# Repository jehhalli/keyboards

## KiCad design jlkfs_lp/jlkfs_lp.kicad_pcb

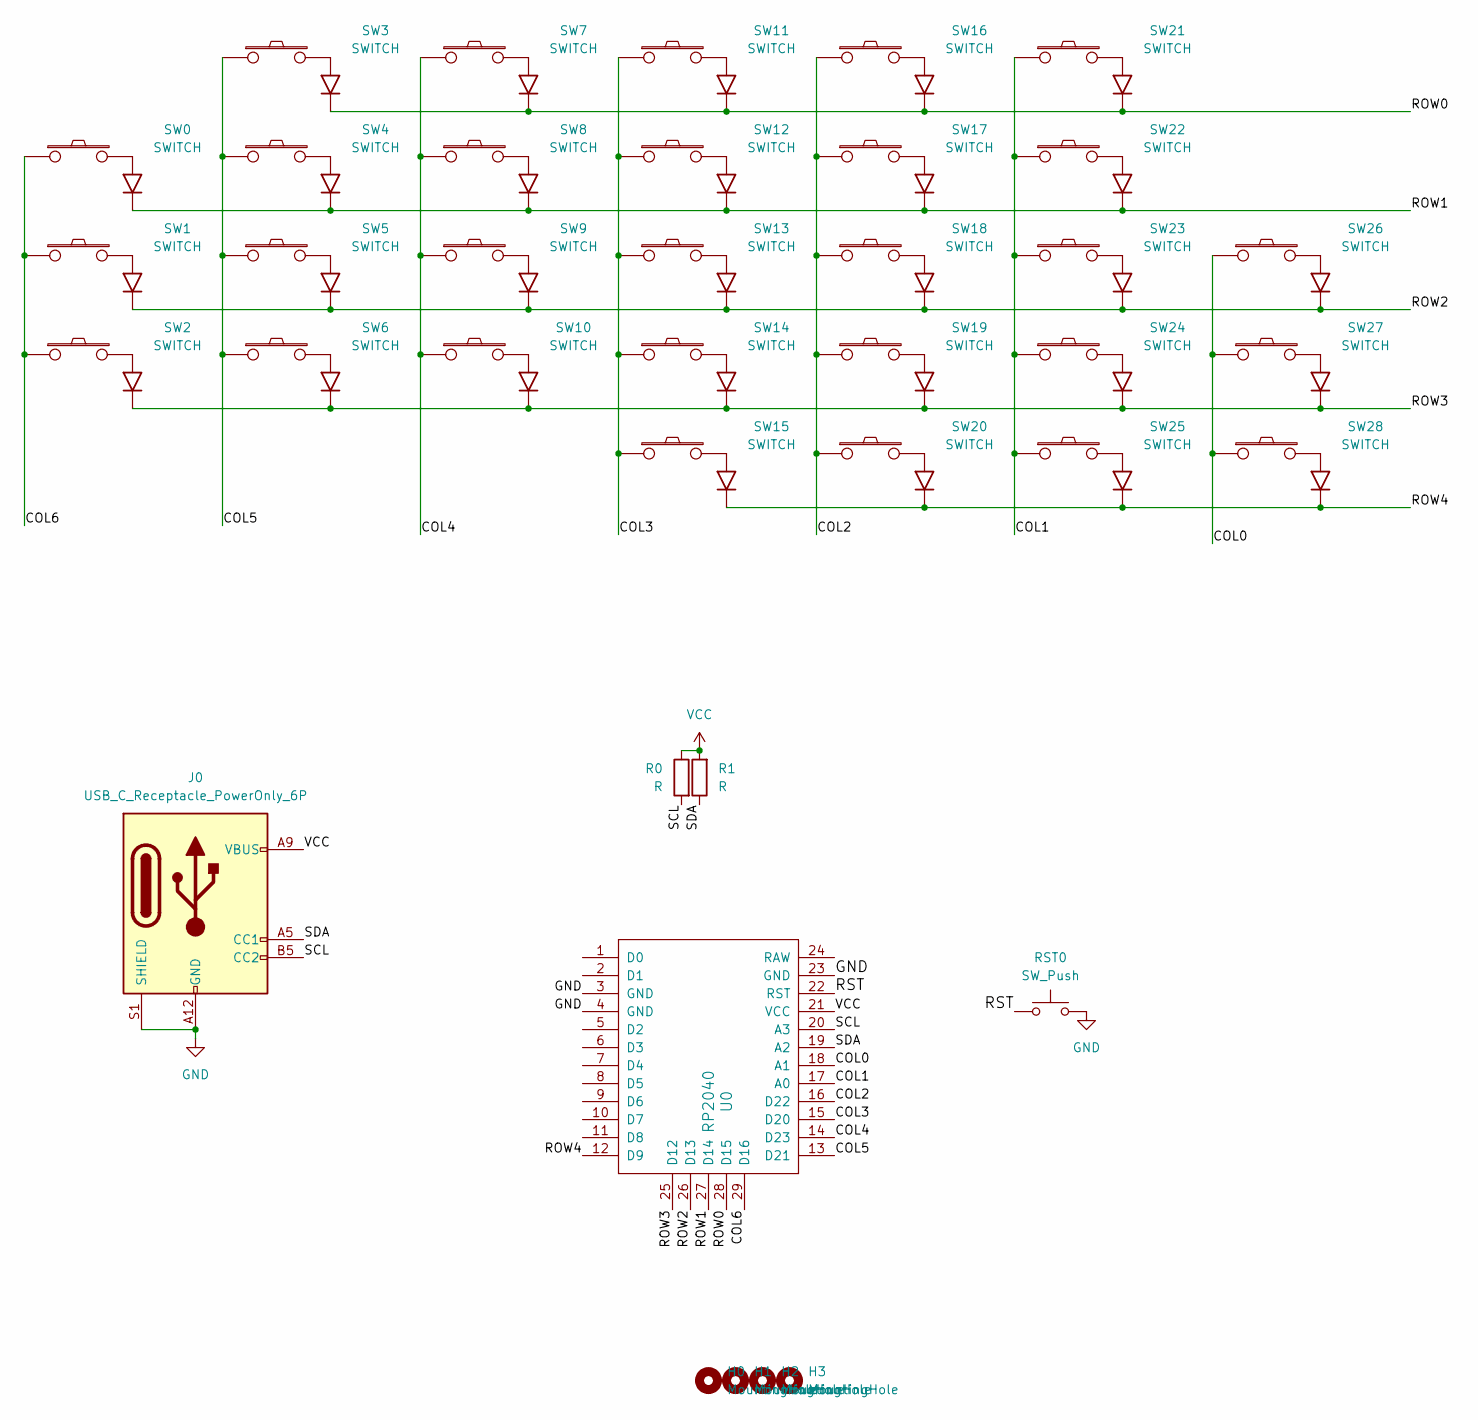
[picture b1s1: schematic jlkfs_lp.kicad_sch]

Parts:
H0, H1, H2, H3: MountingHole; MountingHole_3.5mm
J0: USB_C_Receptacle_PowerOnly_6P; USB4515
R0, R1: R; R_Axial_DIN0204_L3.6mm_D1.6mm_P5.08mm_Horizontal
RST0: SW_Push; reset_button
SW0, SW1, SW2, SW3, SW4, SW5, SW10, SW15, SW20, SW25, SW28: SWITCH; kailh_choc_dual_with_side_diode
SW6, SW7, SW8, SW9, SW11, SW12, SW13, SW14, SW16, SW17, SW18, SW19, SW21, SW22, SW23, SW24, SW26, SW27: SWITCH; kailh_choc_dual_with_diode
U0: RP2040; pro_micro_castellated

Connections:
/COL0: SW26.1, SW27.1, SW28.1, U0.18 (A1)
/COL1: SW21.1, SW22.1, SW23.1, SW24.1, SW25.1, U0.17 (A0)
/COL2: SW16.1, SW17.1, SW18.1, SW19.1, SW20.1, U0.16 (D22)
/COL3: SW11.1, SW12.1, SW13.1, SW14.1, SW15.1, U0.15 (D20)
/COL4: SW7.1, SW8.1, SW9.1, SW10.1, U0.14 (D23)
/COL5: SW3.1, SW4.1, SW5.1, SW6.1, U0.13 (D21)
/COL6: SW0.1, SW1.1, SW2.1, U0.29 (D16)
/ROW0: SW3.3 (K), SW7.3 (K), SW11.3 (K), SW16.3 (K), SW21.3 (K), U0.28 (D15)
/ROW1: SW0.3 (K), SW4.3 (K), SW8.3 (K), SW12.3 (K), SW17.3 (K), SW22.3 (K), U0.27 (D14)
/ROW2: SW1.3 (K), SW5.3 (K), SW9.3 (K), SW13.3 (K), SW18.3 (K), SW23.3 (K), SW26.3 (K), U0.26 (D13)
/ROW3: SW2.3 (K), SW6.3 (K), SW10.3 (K), SW14.3 (K), SW19.3 (K), SW24.3 (K), SW27.3 (K), U0.25 (D12)
/ROW4: SW15.3 (K), SW20.3 (K), SW25.3 (K), SW28.3 (K), U0.12 (D9)
/RST: RST0.1, U0.22 (RST)
/SCL: J0.B5 (CC2), R0.2, U0.20 (A3)
/SDA: J0.A5 (CC1), R1.1, U0.19 (A2)
GND: J0.A12 (GND), J0.B12 (GND), J0.S1 (SHIELD), RST0.2, U0.3 (GND), U0.4 (GND), U0.23 (GND)
VCC: J0.A9 (VBUS), J0.B9 (VBUS), R0.1, R1.2, U0.21 (VCC)

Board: 2 copper layers, 38 parts (12 on the bottom side), 17 nets, no tracks yet.

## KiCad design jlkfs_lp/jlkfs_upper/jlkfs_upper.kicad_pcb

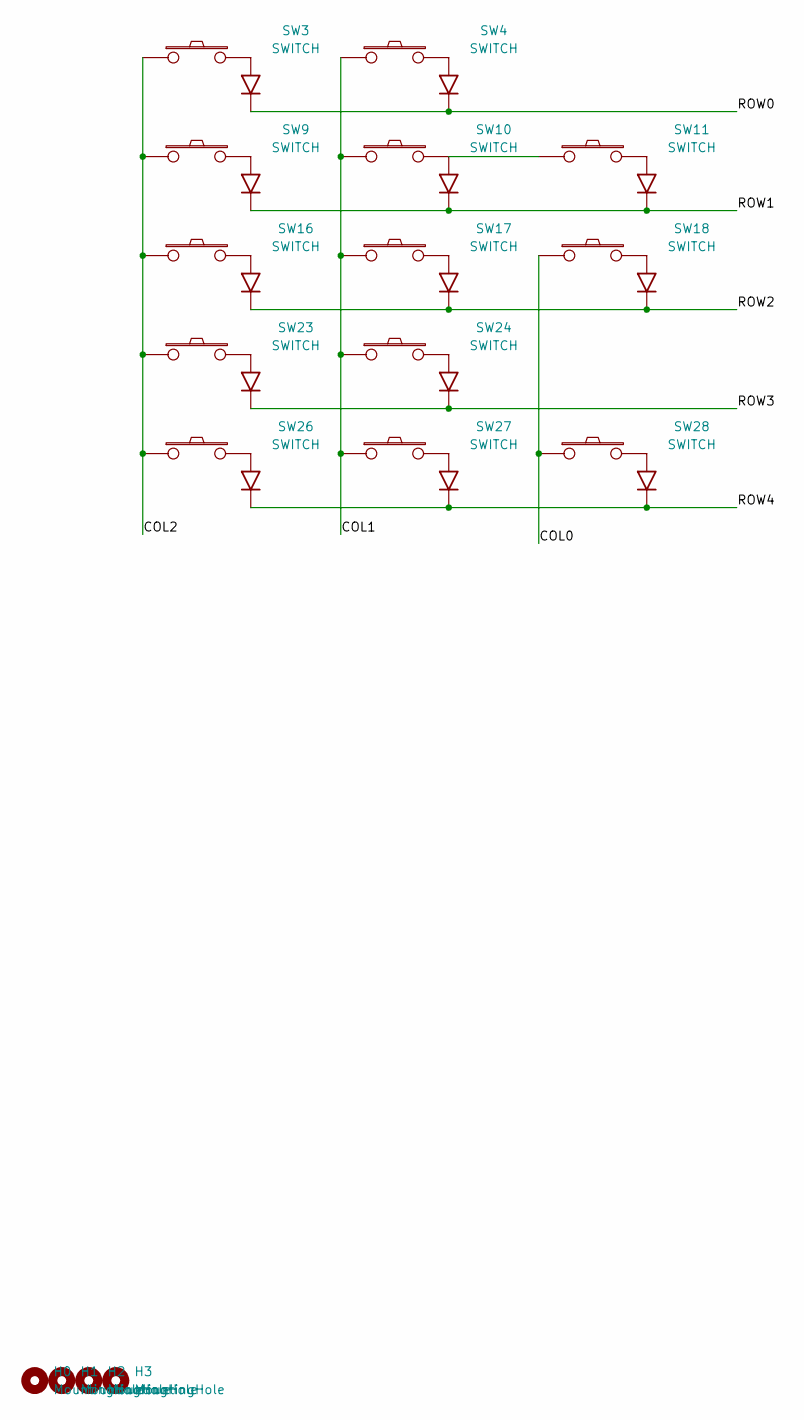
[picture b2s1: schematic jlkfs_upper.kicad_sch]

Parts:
H0, H1, H2, H3: MountingHole; MountingHole_3.5mm
SW3, SW4, SW9, SW10, SW11, SW16, SW17, SW18, SW23, SW24, SW26: SWITCH; kailh_choc_dual_with_diode
SW27, SW28: SWITCH; kailh_choc_dual_with_diode_15

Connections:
/COL0: SW18.1, SW28.1
/COL1: SW4.1, SW10.1, SW17.1, SW24.1, SW27.1
/COL2: SW3.1, SW9.1, SW16.1, SW23.1, SW26.1
/ROW0: SW3.3 (K), SW4.3 (K)
/ROW1: SW9.3 (K), SW10.3 (K), SW11.3 (K)
/ROW2: SW16.3 (K), SW17.3 (K), SW18.3 (K)
/ROW3: SW23.3 (K), SW24.3 (K)
/ROW4: SW26.3 (K), SW27.3 (K), SW28.3 (K)
unnamed: SW10.2, SW11.1

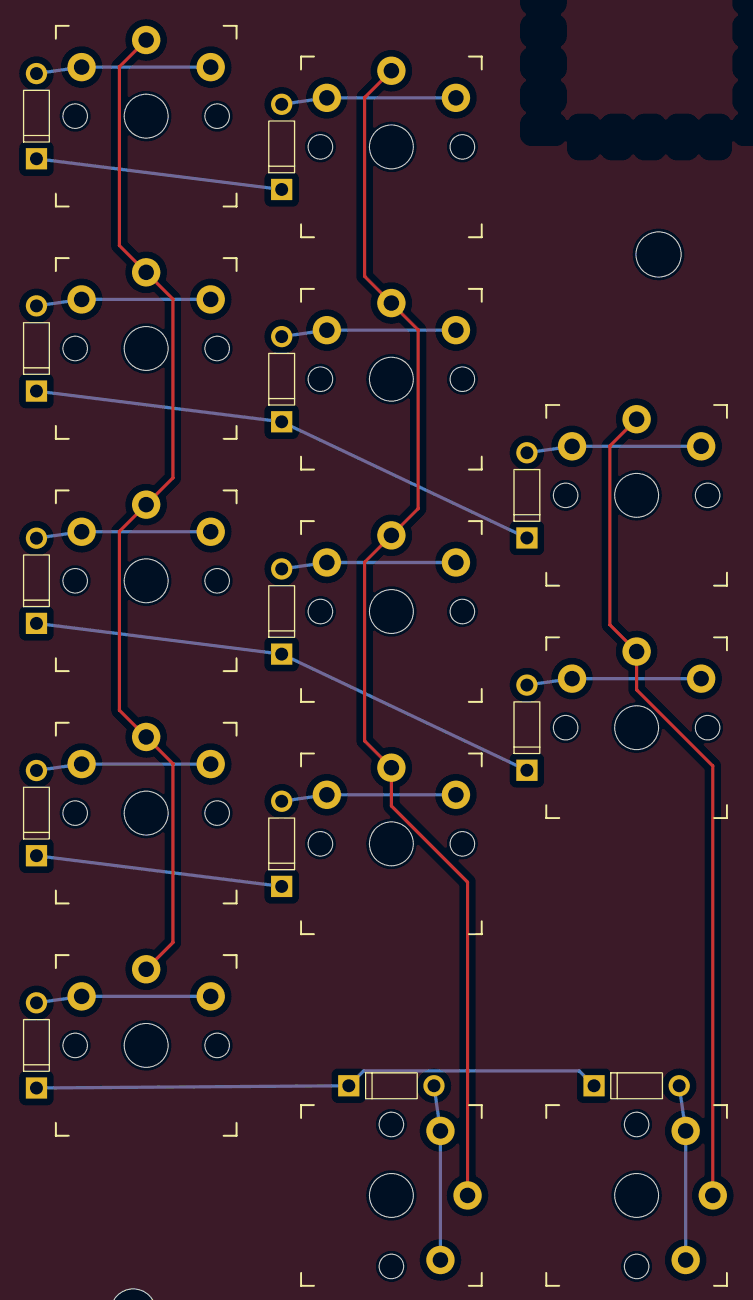
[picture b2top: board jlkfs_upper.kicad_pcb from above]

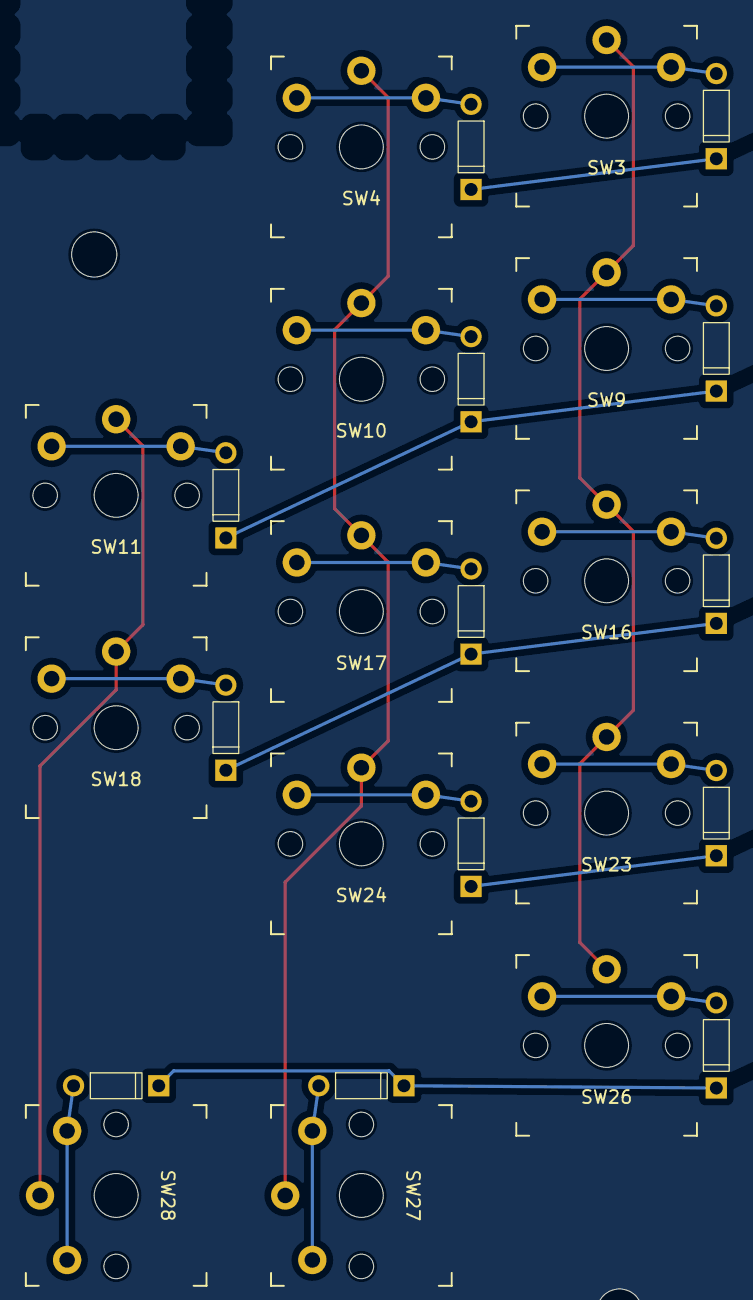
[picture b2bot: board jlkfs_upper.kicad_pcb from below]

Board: 2 copper layers, 17 parts (13 on the bottom side), 9 nets.

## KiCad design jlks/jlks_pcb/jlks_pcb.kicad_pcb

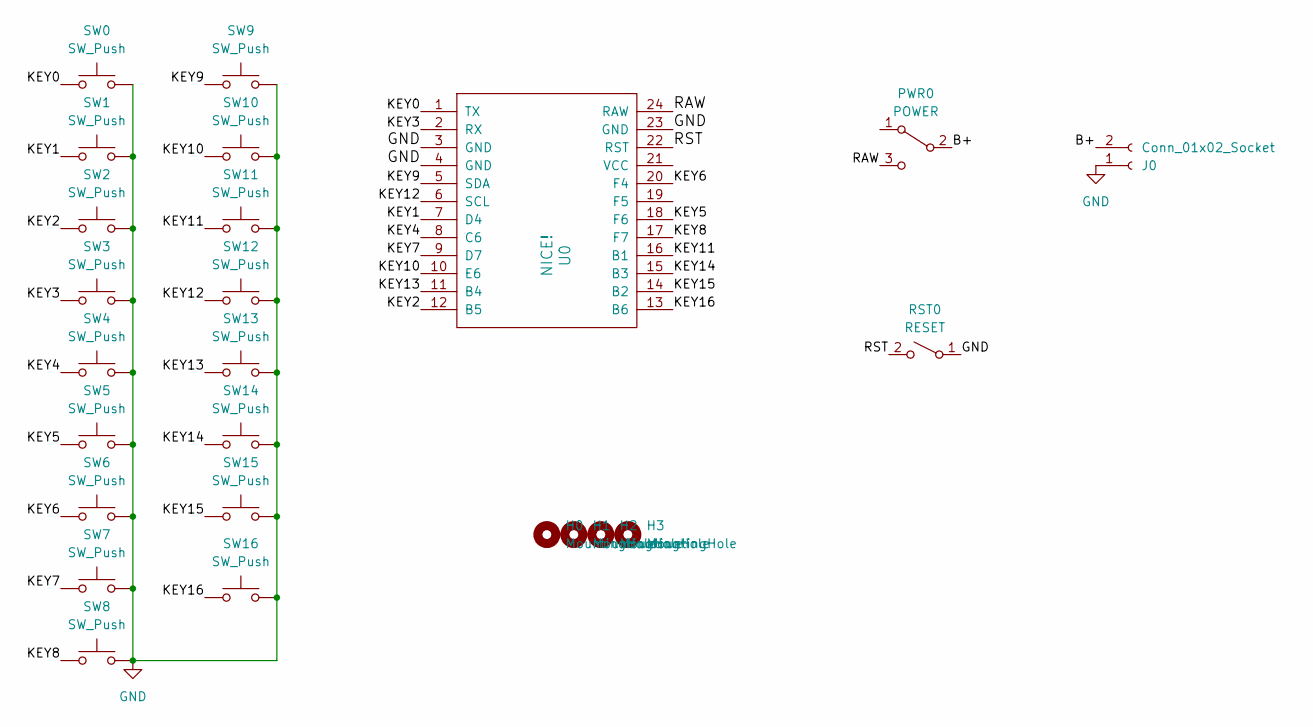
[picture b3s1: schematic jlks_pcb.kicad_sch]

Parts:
H0, H1, H2, H3: MountingHole; MountingHole_3.5mm
J0: Conn_01x02_Socket; PinHeader_1x02_P2.54mm_Vertical
PWR0: POWER; power_switch_1
RST0: RESET; reset_button
SW0, SW1, SW2, SW3, SW4, SW5, SW6, SW7, SW8, SW9, SW10, SW11, SW12, SW13, SW14, SW15, SW16: SW_Push; cherry_hotswap_dual
U0: NICE!; nice!nano

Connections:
/B+: J0.2, PWR0.2 (B)
/KEY0: SW0.2, U0.1 (TX)
/KEY1: SW1.2, U0.7 (D4)
/KEY2: SW2.2, U0.12 (B5)
/KEY3: SW3.2, U0.2 (RX)
/KEY4: SW4.2, U0.8 (C6)
/KEY5: SW5.2, U0.18 (F6)
/KEY6: SW6.1, U0.20 (F4)
/KEY7: SW7.1, U0.9 (D7)
/KEY8: SW8.1, U0.17 (F7)
/KEY9: SW9.2, U0.5 (SDA)
/KEY10: SW10.2, U0.10 (E6)
/KEY11: SW11.2, U0.16 (B1)
/KEY12: SW12.2, U0.6 (SCL)
/KEY13: SW13.2, U0.11 (B4)
/KEY14: SW14.2, U0.15 (B3)
/KEY15: SW15.2, U0.14 (B2)
/KEY16: SW16.1, U0.13 (B6)
/RAW: PWR0.3 (C), U0.24 (RAW)
/RST: RST0.2 (B), U0.22 (RST)
GND: J0.1, RST0.1 (A), SW0.1, SW1.1, SW2.1, SW3.1, SW4.1, SW5.1, SW6.2, SW7.2, SW8.2, SW9.1, SW10.1, SW11.1, SW12.1, SW13.1, SW14.1, SW15.1, SW16.2, U0.3 (GND), U0.4 (GND), U0.23 (GND)

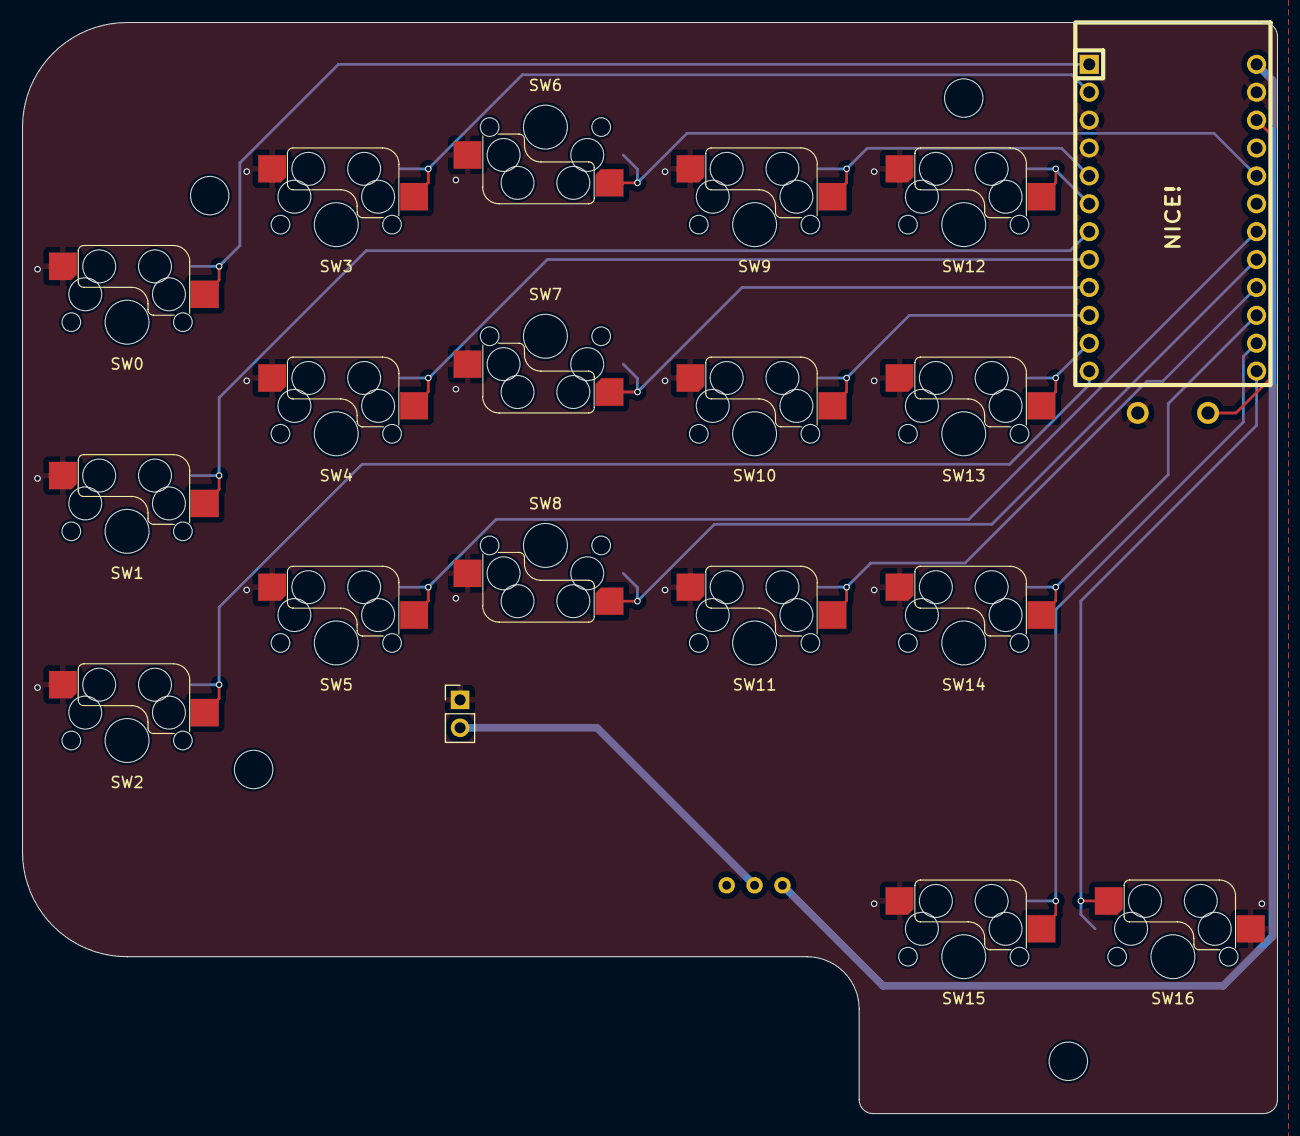
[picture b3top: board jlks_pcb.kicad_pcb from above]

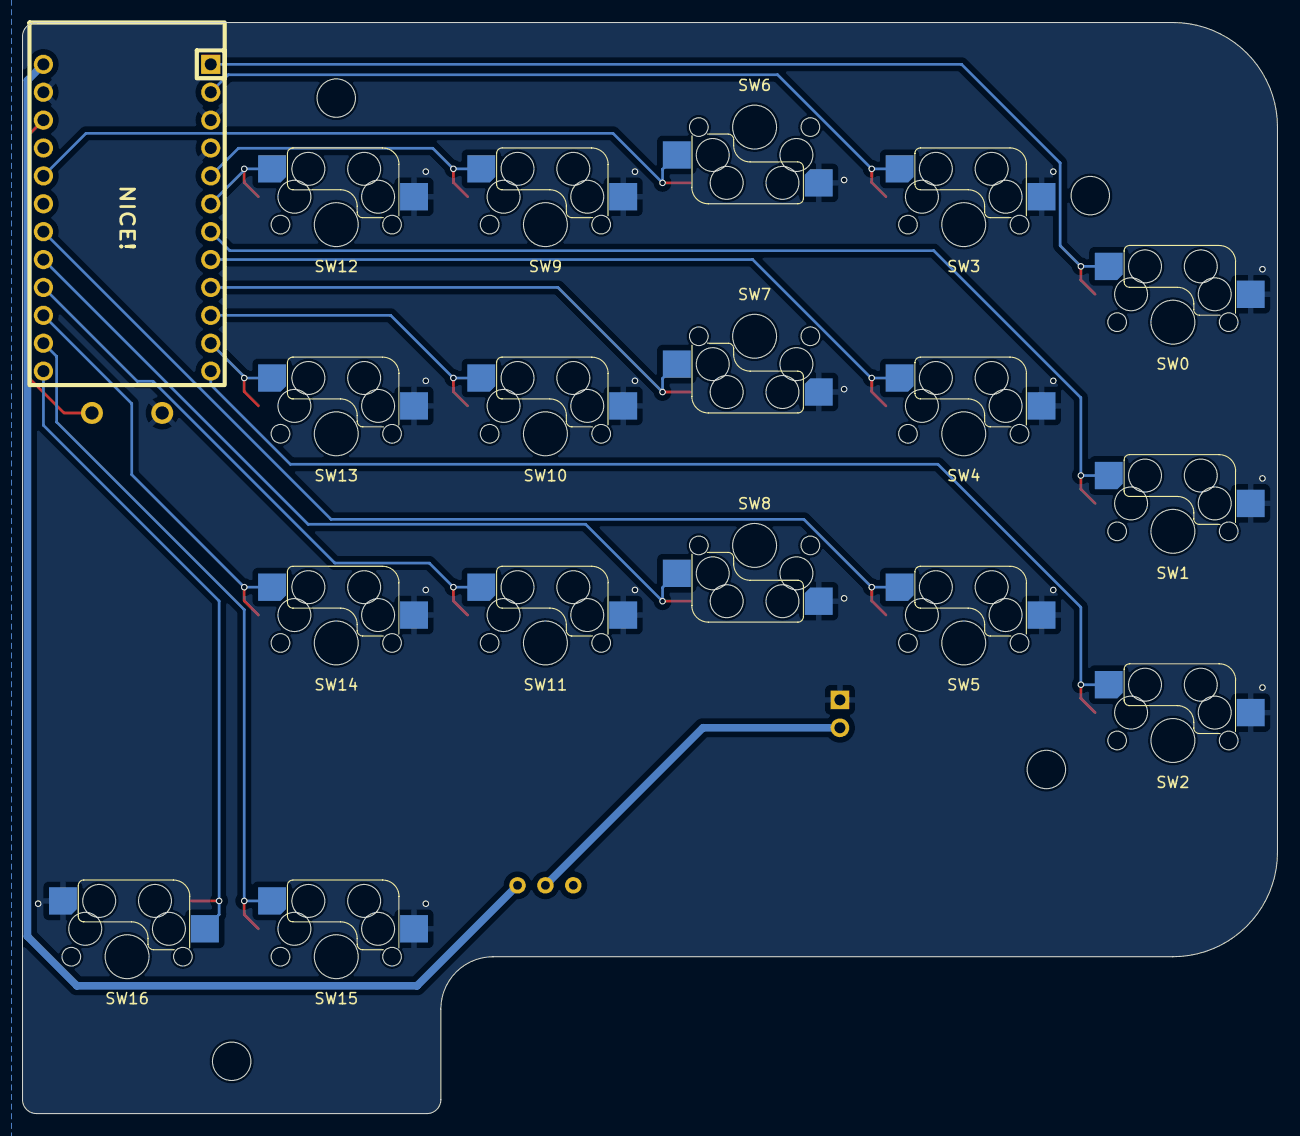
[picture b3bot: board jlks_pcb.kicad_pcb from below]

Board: 2 copper layers, 114.3 x 99.4 mm, 25 parts (2 on the bottom side), 21 nets.

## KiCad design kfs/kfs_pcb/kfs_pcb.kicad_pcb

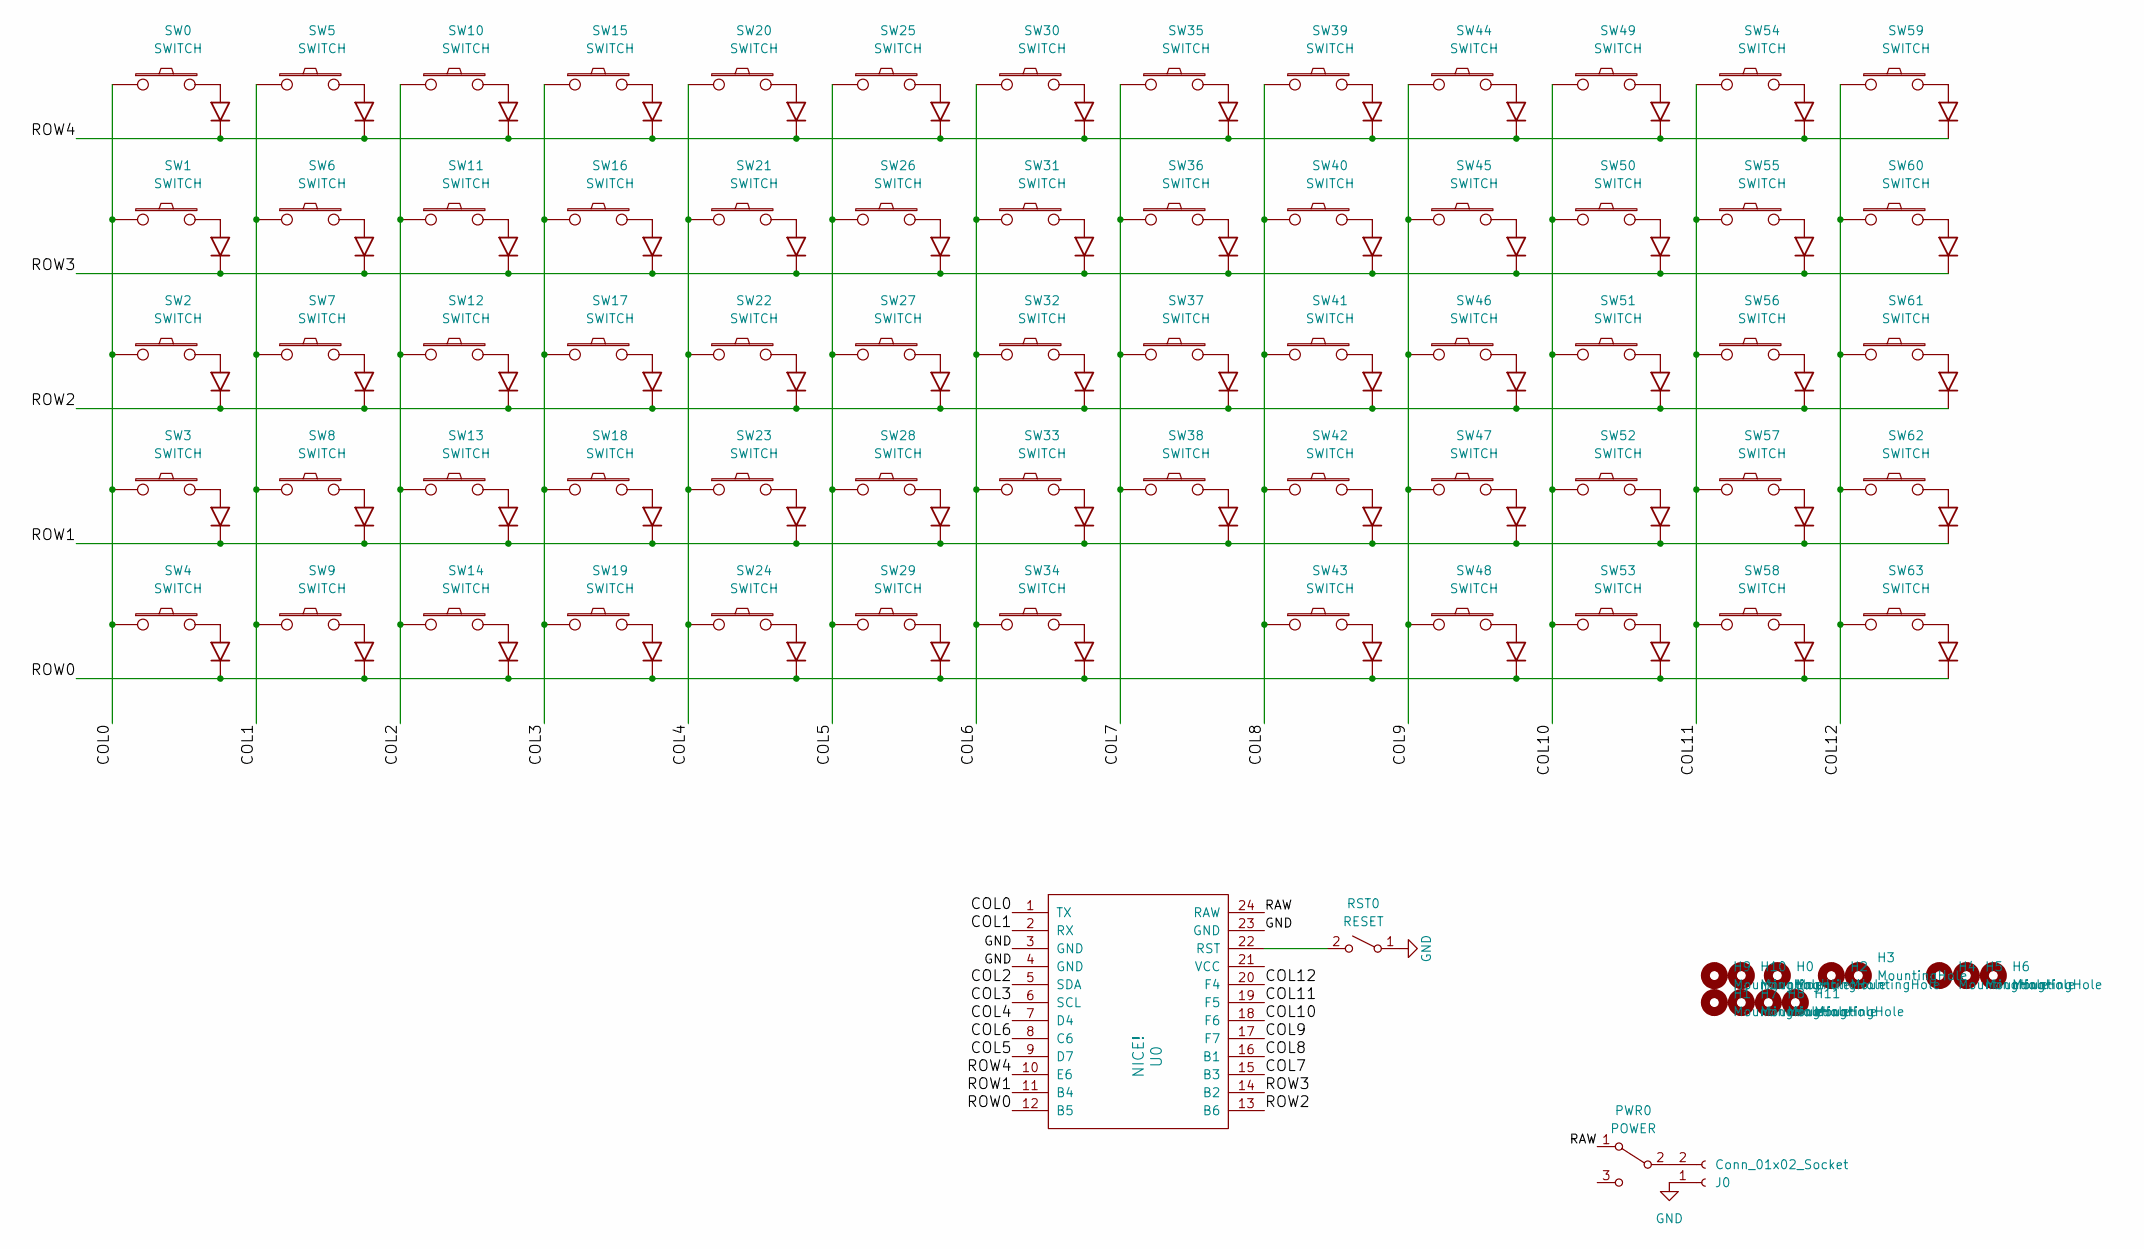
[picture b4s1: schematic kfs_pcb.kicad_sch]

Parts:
H0, H1, H2, H3, H4, H5, H6, H7, H8, H9, H10, H11: MountingHole; MountingHole_3.5mm
J0: Conn_01x02_Socket; jst_ph
PWR0: POWER; power_switch
RST0: RESET; reset_button_2
SW0, SW1, SW2, SW3, SW4, SW5, SW6, SW7, SW8, SW9, SW10, SW11, SW12, SW13, SW14, SW15, SW16, SW17, SW18, SW19, SW20, SW21, SW22, SW23, SW24, SW25, SW26, SW27, SW28, SW29, SW30, SW31, SW32, SW33, SW34, SW35, SW36, SW37, SW38, SW39, SW40, SW41, SW42, SW43, SW44, SW45, SW46, SW47, SW48, SW49, SW50, SW51, SW52, SW53, SW54, SW55, SW56, SW57, SW58, SW59, SW60, SW61, SW62, SW63: SWITCH; kailh_choc_with_diode
U0: NICE!; nice!nano

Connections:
/COL0: SW0.1, SW1.1, SW2.1, SW3.1, SW4.1, U0.1 (TX)
/COL1: SW5.1, SW6.1, SW7.1, SW8.1, SW9.1, U0.2 (RX)
/COL2: SW10.1, SW11.1, SW12.1, SW13.1, SW14.1, U0.5 (SDA)
/COL3: SW15.1, SW16.1, SW17.1, SW18.1, SW19.1, U0.6 (SCL)
/COL4: SW20.1, SW21.1, SW22.1, SW23.1, SW24.1, U0.7 (D4)
/COL5: SW25.1, SW26.1, SW27.1, SW28.1, SW29.1, U0.9 (D7)
/COL6: SW30.1, SW31.1, SW32.1, SW33.1, SW34.1, U0.8 (C6)
/COL7: SW35.1, SW36.1, SW37.1, SW38.1, U0.15 (B3)
/COL8: SW39.1, SW40.1, SW41.1, SW42.1, SW43.1, U0.16 (B1)
/COL9: SW44.1, SW45.1, SW46.1, SW47.1, SW48.1, U0.17 (F7)
/COL10: SW49.1, SW50.1, SW51.1, SW52.1, SW53.1, U0.18 (F6)
/COL11: SW54.1, SW55.1, SW56.1, SW57.1, SW58.1, U0.19 (F5)
/COL12: SW59.1, SW60.1, SW61.1, SW62.1, SW63.1, U0.20 (F4)
/RAW: PWR0.1 (A), U0.24 (RAW)
/ROW0: SW4.3 (K), SW9.3 (K), SW14.3 (K), SW19.3 (K), SW24.3 (K), SW29.3 (K), SW34.3 (K), SW43.3 (K), SW48.3 (K), SW53.3 (K), SW58.3 (K), SW63.3 (K), U0.12 (B5)
/ROW1: SW3.3 (K), SW8.3 (K), SW13.3 (K), SW18.3 (K), SW23.3 (K), SW28.3 (K), SW33.3 (K), SW38.3 (K), SW42.3 (K), SW47.3 (K), SW52.3 (K), SW57.3 (K), SW62.3 (K), U0.11 (B4)
/ROW2: SW2.3 (K), SW7.3 (K), SW12.3 (K), SW17.3 (K), SW22.3 (K), SW27.3 (K), SW32.3 (K), SW37.3 (K), SW41.3 (K), SW46.3 (K), SW51.3 (K), SW56.3 (K), SW61.3 (K), U0.13 (B6)
/ROW3: SW1.3 (K), SW6.3 (K), SW11.3 (K), SW16.3 (K), SW21.3 (K), SW26.3 (K), SW31.3 (K), SW36.3 (K), SW40.3 (K), SW45.3 (K), SW50.3 (K), SW55.3 (K), SW60.3 (K), U0.14 (B2)
/ROW4: SW0.3 (K), SW5.3 (K), SW10.3 (K), SW15.3 (K), SW20.3 (K), SW25.3 (K), SW30.3 (K), SW35.3 (K), SW39.3 (K), SW44.3 (K), SW49.3 (K), SW54.3 (K), SW59.3 (K), U0.10 (E6)
GND: J0.1, PWR0.0, RST0.1 (A), U0.3 (GND), U0.4 (GND), U0.23 (GND)
unnamed: J0.2, PWR0.2 (B)
unnamed: RST0.2 (B), U0.22 (RST)

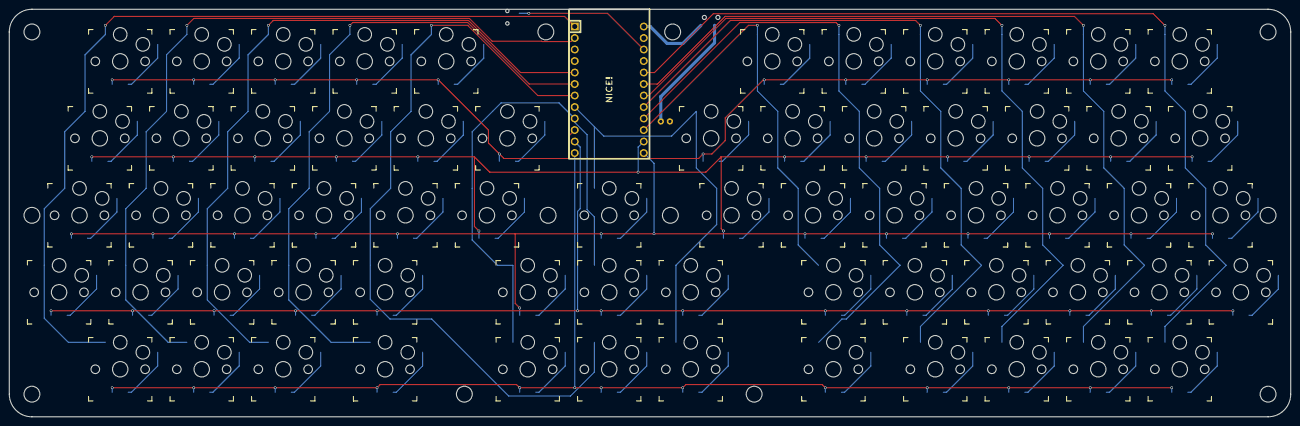
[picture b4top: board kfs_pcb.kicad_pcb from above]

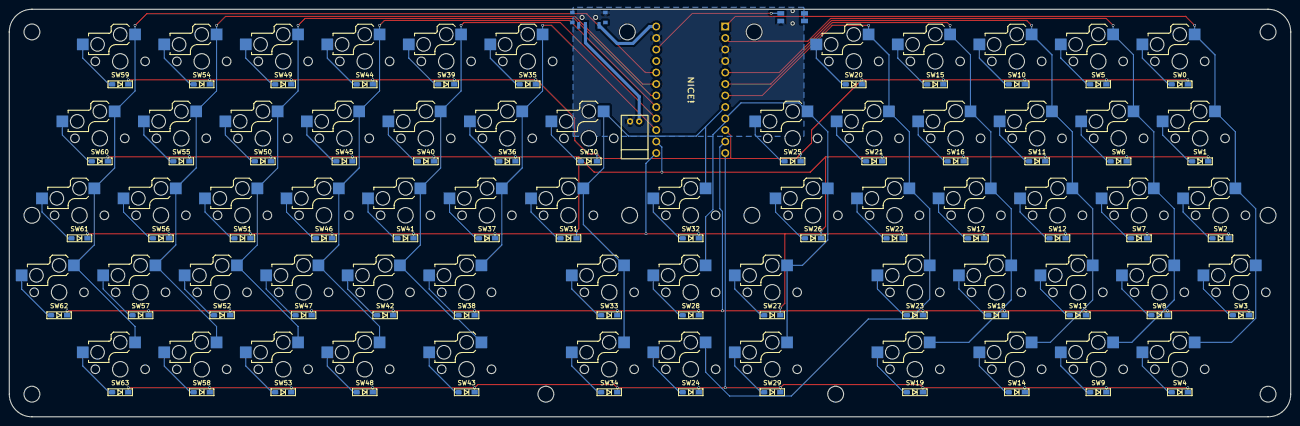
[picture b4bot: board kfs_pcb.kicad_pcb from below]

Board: 2 copper layers, 283.0 x 90.0 mm, 80 parts (3 on the bottom side), 22 nets.
